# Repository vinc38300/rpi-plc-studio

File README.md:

# RPi-PLC Studio

Atelier de programmation PLC en **FBD** (Function Block Diagram) pour Raspberry Pi, avec déploiement à distance, supervision web (synoptique/SCADA) et pont domotique MQTT.

Conçu à l'origine pour piloter une installation de chauffage (solaire thermique + chaudière + plancher chauffant), mais utilisable pour tout automatisme à base de GPIO/I²C sur Raspberry Pi.

## Sommaire

- [Aperçu](#aperçu)
- [Architecture](#architecture)
- [Fonctionnalités](#fonctionnalités)
- [Installation](#installation)
- [Démarrage rapide](#démarrage-rapide)
- [Structure du dépôt](#structure-du-dépôt)
- [Déploiement](#déploiement)
- [Limitations connues](#limitations-connues)
- [Licence](#licence)

## Aperçu

RPi-PLC Studio se compose de deux applications distinctes :

- **Studio** (PC Linux, PyQt5) : éditeur graphique FBD pour construire la logique de l'automate, simulateur intégré, éditeur de synoptique, et gestion du déploiement SSH.
- **Serveur RPi** (Raspberry Pi, Flask) : exécute le programme compilé en temps réel, pilote les GPIO/ADS1115, expose une interface web de supervision, et communique avec des services externes (MQTT, Telegram).

Le programme est conçu sur PC dans le Studio, puis transféré sur le Raspberry Pi par SSH/SFTP en un clic.

## Architecture

```
┌─────────────────────────┐         SSH / SFTP          ┌──────────────────────────┐
│   RPi-PLC Studio (PC)    │ ───────────────────────────▶│   Serveur RPi (Flask)     │
│                          │                              │                          │
│  • Éditeur FBD (PyQt5)   │                              │  • Moteur PLC (scan 100ms)│
│  • Simulation locale     │                              │  • GPIO (gpiod/lgpio)     │
│  • Éditeur synoptique    │                              │  • ADS1115 (sondes NTC)   │
│  • core/deployer.py      │                              │  • Web SCADA + synoptique │
└─────────────────────────┘                              │  • Pont MQTT              │
                                                           │  • Notifications Telegram │
                                                           └──────────────────────────┘
                                                                       │
                                                                MQTT (broker externe)
                                                                       │
                                                          Home Assistant / Venus OS / etc.
```

## Fonctionnalités

- Éditeur FBD complet : blocs logiques (AND/OR/XOR/NOT…), temporisateurs, compteurs, bascules SR, PID, comparateurs, calculs analogiques, capteurs (PT100/PT1000/NTC), connecteurs inter-pages.
- Simulation locale dans le Studio avant tout déploiement.
- Synoptique web personnalisable (widgets température, jauges, commandes, courbes de tendance).
- Programmation horaire hebdomadaire (P5_JOURS) avec consignes par jour.
- Pont MQTT bidirectionnel (Subscribe/Publish) pour intégration domotique externe.
- Notifications Telegram (alarmes, rapport quotidien).
- Sauvegardes automatiques du programme à chaque déploiement.
- Diagnostic intelligent du Raspberry Pi avant déploiement (`smart_check`) : détecte les paquets manquants, les fichiers serveur obsolètes, et propose l'action adaptée (programme seul / mise à jour service / installation complète).

## Installation

### Studio (PC Linux — Ubuntu 22.04+, Debian 12+)

```bash
sudo apt install ./rpi-plc-studio_3.4-1.deb
```

ou depuis les sources :

```bash
sudo bash install-studio.sh
```

### Serveur (Raspberry Pi — Bookworm/Bullseye, 32 ou 64 bits)

```bash
sudo dpkg -i rpi-plc_3.4-serveur-arm64.deb && sudo apt-get install -f
```

ou depuis les sources :

```bash
sudo bash install.sh
```

Dépendances installées automatiquement : `python3-gpiod` (v2, GPIO natif Bookworm) ou `lgpio` en repli, `flask`, `flask-socketio`, `smbus2` (ADS1115), `requests`.

> **Pont MQTT (optionnel)** : `paho-mqtt` n'est pas installé automatiquement par `install.sh`. Si vous utilisez le bloc MQTT, installez-le manuellement sur le RPi : `pip3 install paho-mqtt --break-system-packages`.

## Démarrage rapide

1. Lancer le Studio, créer un nouveau projet ou ouvrir un `.plcproj` existant.
2. Construire la logique dans l'éditeur FBD (glisser-déposer depuis la palette).
3. Tester en simulation locale (bouton **START**).
4. Configurer la connexion SSH du Raspberry Pi (menu **Raspberry Pi → Déployer**).
5. Cliquer sur **🔍 Scanner réseau** puis **Analyser** pour un diagnostic automatique, ou directement **🚀 Déployer**.
6. Ouvrir l'interface web de supervision : `http://<ip-du-rpi>:5000/scada`.

## Structure du dépôt

```
.
├── core/                   # Moteur PLC (simulation) et logique de déploiement
│   ├── plc_engine.py       # Compilation FBD → exécution (utilisé par le Studio uniquement)
│   ├── deployer.py         # Connexion SSH/SFTP, smart_check, deploy()/deploy_prog_only()
│   └── project.py          # Sérialisation des fichiers .plcproj
├── ui/                     # Interface PyQt5 du Studio
│   ├── main_window.py
│   ├── block_editor.py     # Compilation des blocs FBD → JSON
│   ├── fbd_canvas.js       # Canvas FBD (HTML/JS embarqué via QWebEngine)
│   ├── synoptic_canvas.js  # Éditeur de synoptique
│   ├── deploy_dialog.py    # Fenêtre de déploiement
│   └── rpi_monitor.py      # Monitoring temps réel du RPi connecté
├── rpi_server/             # Tout ce qui s'exécute réellement sur le Raspberry Pi
│   ├── server.py           # Serveur Flask + moteur PLC temps réel (le vrai moteur en prod)
│   ├── mqtt_bridge.py       # Pont MQTT Subscribe/Publish
│   ├── telegram_bot.py
│   ├── auth.py / backup_manager.py / recipes.py / calibration.py / report_generator.py
│   ├── templates/          # Pages web (SCADA, synoptique desktop/mobile)
│   ├── static/             # JS/CSS/icônes servis par Flask
│   └── rpi-plc.service     # Unit systemd
├── resources/              # Thèmes Qt, icônes, documentation HTML
├── install.sh               # Installation serveur RPi depuis les sources
├── install-studio.sh        # Installation Studio PC depuis les sources
└── *.deb                    # Paquets pré-construits (arm64 + amd64)
```

> **Point d'attention architectural** : `core/plc_engine.py` (et sa copie dans `resources/`) ne sert qu'à la **simulation locale dans le Studio**. Le moteur qui tourne réellement en production sur le Raspberry Pi est une classe `PLCEngine` distincte, intégrée directement dans `rpi_server/server.py`. Toute correction de la logique d'exécution doit être appliquée aux **deux** endroits si elle doit être visible en simulation *et* en production.

## Déploiement

Le Studio propose deux modes, tous deux gérés par `core/deployer.py` :

| Mode | Déclenché par | Transfère |
|---|---|---|
| **Programme seul** | `deploy_prog_only()` | `programme.json`, `synoptic.json`, `config.json` (fusion GPIO/sondes), et **tous les fichiers de `SERVER_FILES`** (mise à jour silencieuse si nécessaire) |
| **Complet** | `deploy()` | Idem + arrêt propre du service, libération GPIO, redémarrage du serveur |

`smart_check()` analyse le Raspberry Pi avant déploiement (OS, GPIO, dépendances Python, fichiers serveur présents/à jour, état du service) et recommande l'action adaptée.

> **⚠ Ajouter un nouveau fichier serveur** (ex. un futur `xyz_bridge.py` dans `rpi_server/`) **ne suffit pas** à le faire déployer automatiquement : il doit explicitement être ajouté à la liste `SERVER_FILES` en tête de `core/deployer.py`, sinon aucun bouton de déploiement ne le transférera jamais, même après des dizaines de déploiements répétés.

## Limitations connues

- `install.sh` ne vérifie/installe pas `paho-mqtt` automatiquement (à faire manuellement si le bloc MQTT est utilisé).
- Le moteur de simulation Studio (`core/plc_engine.py`) et le moteur de production (`rpi_server/server.py`) sont deux implémentations distinctes qui doivent être maintenues en parallèle.
- `smart_check()` compare les fichiers par **taille** (pas par hash) — un fichier modifié mais de taille identique au fichier distant ne sera pas détecté comme obsolète.

## Licence

[GPLv3](LICENSE) (GNU General Public License v3.0).

Concrètement : n'importe qui peut utiliser, étudier et modifier le code librement, y compris à des fins commerciales — mais toute version modifiée ou redistribuée doit rester sous GPLv3 et son code source doit être fourni aux destinataires. Il est donc impossible pour un tiers de prendre ce projet, de le fermer, et de le revendre sans en redonner le code source.

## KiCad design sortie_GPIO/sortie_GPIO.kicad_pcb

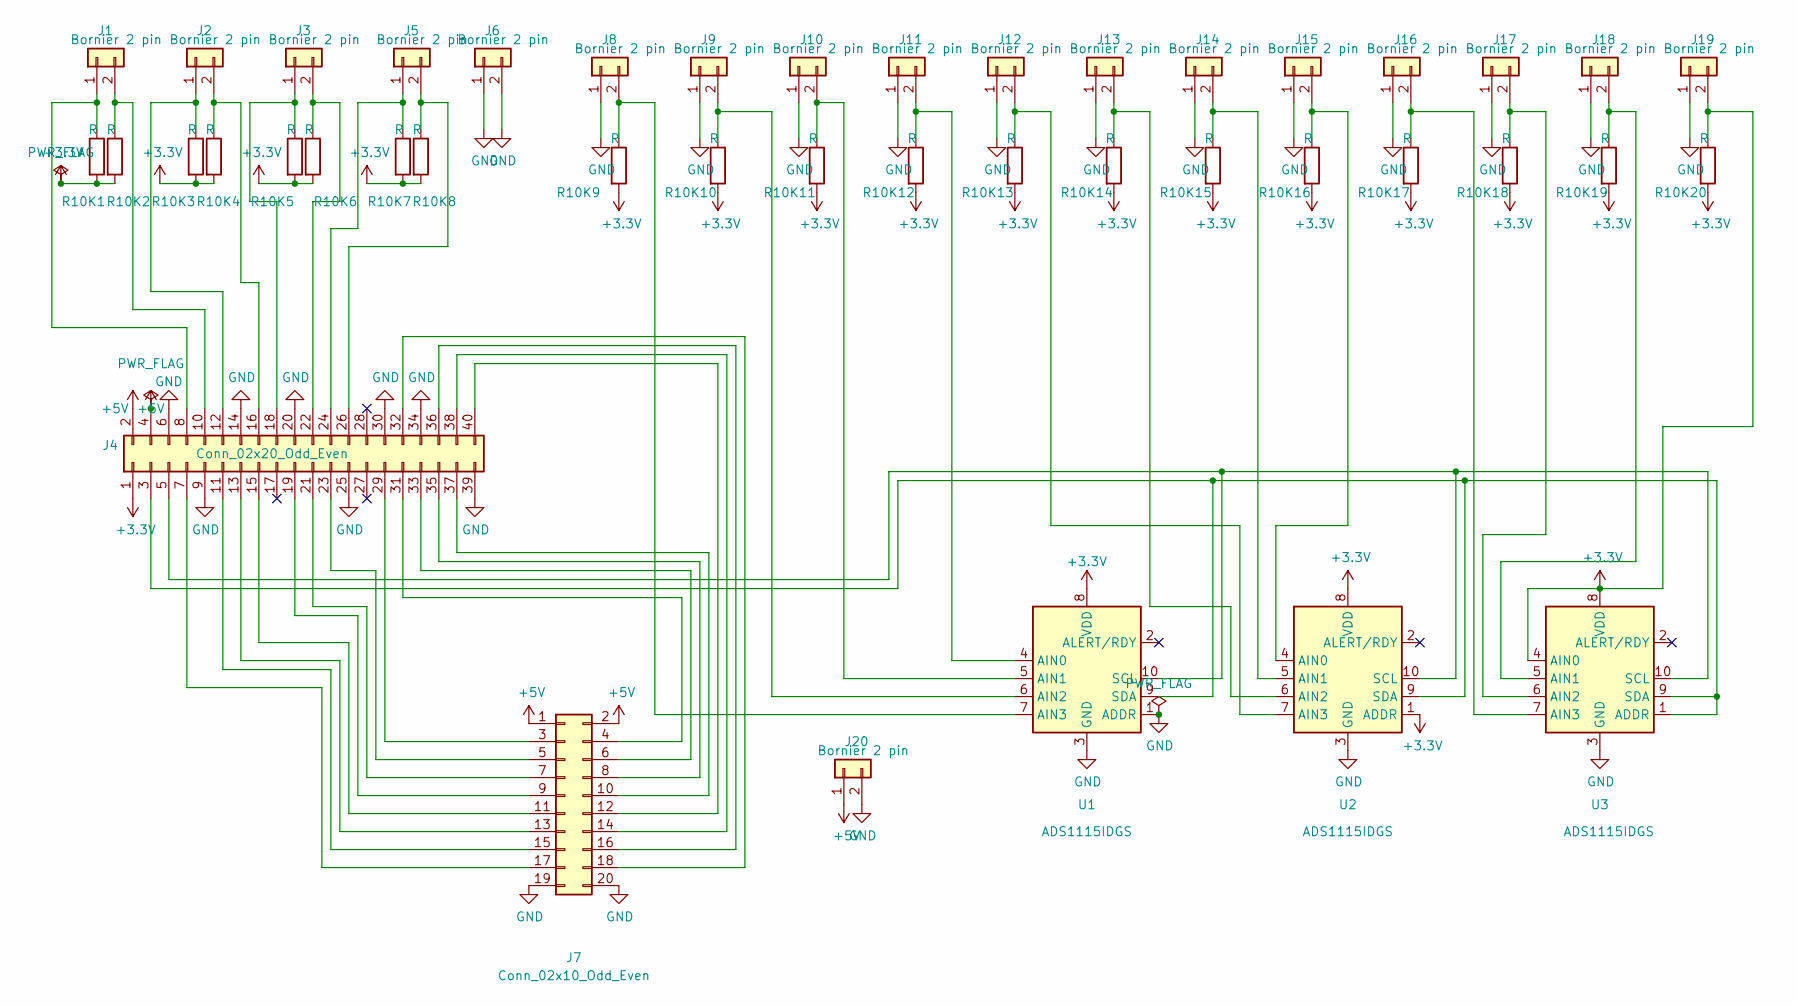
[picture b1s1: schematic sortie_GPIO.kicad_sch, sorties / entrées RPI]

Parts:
J1, J2, J3, J5, J6, J8, J9, J10, J11, J12, J13, J14, J15, J16, J17, J18, J19, J20: Bornier 2 pin; TerminalBlock_bornier-2_P5.08mm
J4: Conn_02x20_Odd_Even; PinHeader_2x20_P2.54mm_Vertical
J7: Conn_02x10_Odd_Even; PinHeader_2x10_P2.54mm_Vertical
R10K1, R10K2, R10K3, R10K4, R10K5, R10K6, R10K7, R10K8, R10K9, R10K10, R10K11, R10K12, R10K13, R10K14, R10K15, R10K16, R10K17, R10K18, R10K19, R10K20: R; R_Axial_DIN0309_L9.0mm_D3.2mm_P12.70mm_Horizontal
U1, U2, U3: ADS1115IDGS; PinHeader_1x10_P2.54mm_Vertical

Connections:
+3V3: J4.1, J19.2, R10K1.2, R10K2.2, R10K3.2, R10K4.2, R10K5.2, R10K6.2, R10K7.2, R10K8.2, R10K9.2, R10K10.2, R10K11.2, R10K12.2, R10K13.2, R10K14.2, R10K15.2, R10K16.2, R10K17.2, R10K18.2, R10K19.2, R10K20.1, R10K20.2, U1.8 (VDD), U2.1 (ADDR), U2.8 (VDD), U3.4 (AIN0), U3.8 (VDD)
+5V: J4.2, J4.4, J7.1, J7.2, J20.1
GND: J4.6, J4.9, J4.14, J4.20, J4.25, J4.30, J4.34, J4.39, J6.1, J6.2, J7.19, J7.20, J8.1, J9.1, J10.1, J11.1, J12.1, J13.1, J14.1, J15.1, J16.1, J17.1, J18.1, J19.1, J20.2, U1.1 (ADDR), U1.3 (GND), U2.3 (GND), U3.3 (GND)
unnamed: J1.1, J4.8, R10K1.1
unnamed: J1.2, J4.10, R10K2.1
unnamed: J2.1, J4.12, R10K3.1
unnamed: J2.2, J4.16, R10K4.1
unnamed: J3.1, J4.18, R10K5.1
unnamed: J3.2, J4.22, R10K6.1
unnamed: J4.3, U1.9 (SDA), U2.9 (SDA), U3.1 (ADDR), U3.9 (SDA)
unnamed: J4.5, U1.10 (SCL), U2.10 (SCL), U3.10 (SCL)
unnamed: J4.7, J7.17
unnamed: J4.11, J7.15
unnamed: J4.13, J7.13
unnamed: J4.15, J7.11
unnamed: J4.19, J7.9
unnamed: J4.21, J7.7
unnamed: J4.23, J7.5
unnamed: J4.24, J5.1, R10K7.1
unnamed: J4.26, J5.2, R10K8.1
unnamed: J4.29, J7.3
unnamed: J4.31, J7.4
unnamed: J4.32, J7.18
unnamed: J4.33, J7.6
unnamed: J4.35, J7.8
unnamed: J4.36, J7.16
unnamed: J4.37, J7.10
unnamed: J4.38, J7.14
unnamed: J4.40, J7.12
unnamed: J8.2, R10K9.1, U1.7 (AIN3)
unnamed: J9.2, R10K10.1, U1.6 (AIN2)
unnamed: J10.2, R10K11.1, U1.5 (AIN1)
unnamed: J11.2, R10K12.1, U1.4 (AIN0)
unnamed: J12.2, R10K13.1, U2.7 (AIN3)
unnamed: J13.2, R10K14.1, U2.6 (AIN2)
unnamed: J14.2, R10K15.1, U2.5 (AIN1)
unnamed: J15.2, R10K16.1, U2.4 (AIN0)
unnamed: J16.2, R10K17.1, U3.7 (AIN3)
unnamed: J17.2, R10K18.1, U3.6 (AIN2)
unnamed: J18.2, R10K19.1, U3.5 (AIN1)

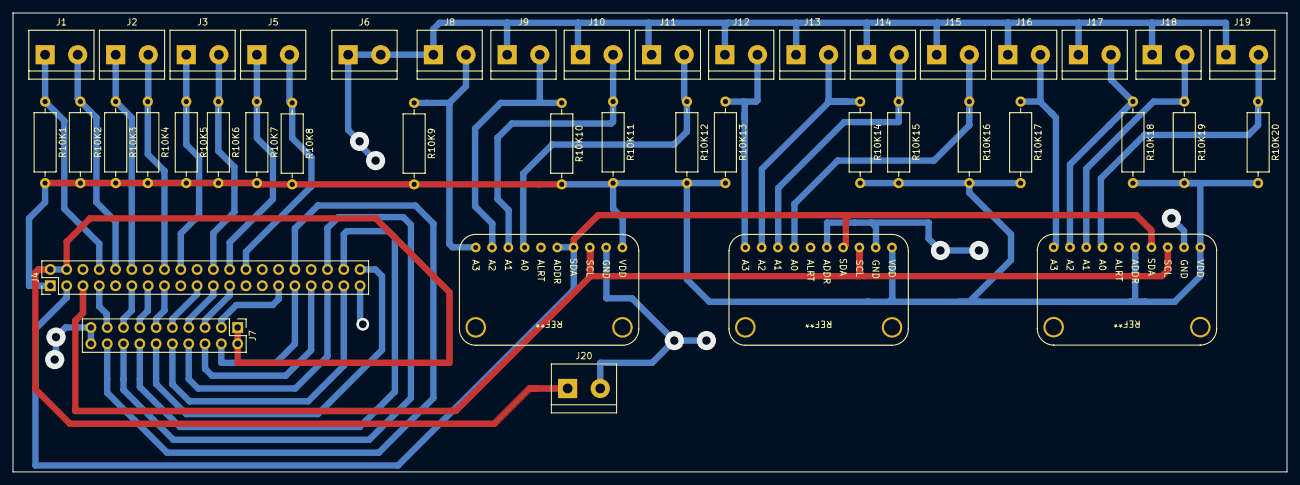
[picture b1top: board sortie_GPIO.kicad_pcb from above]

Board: 2 copper layers, 198.5 x 71.5 mm, 40 parts (0 on the bottom side), 38 nets.

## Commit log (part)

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2026-03-23 rpi-plc-studio
2026-06-12 refonte du code
2026-06-12 gitignore: exclure fichiers cache système
2026-06-12 mise a jour de la doc
2026-06-12 securité
2026-06-12 nom du deb
2026-06-12 nom du deb1
2026-06-12 nom du deb2
2026-06-12 instal
2026-06-16 modif Ballon et ajout block mqtt
2026-06-17 Redame
    Add initial README.md with project overview and documentation
2026-06-18 historisation et deb
2026-06-18 deb new
2026-06-18 Create SECURITY.md for security policy and reporting
    Added a security policy document outlining supported versions and vulnerability reporting.
2026-06-18 Update SSH key path in plcproj file
